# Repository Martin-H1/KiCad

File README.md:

# KiCad

I will post my open source PCB designs here.

Overview
======
The purpose of this repository is to serve as a backup of my projects, as well as a way to

Prerequisites
======
* KiCad 7.0
* Git to fetch these files.

Directories
======
* Mench Reloaded - w65c265 SBC specs similar to the Mench computer from WDC.
* README.md - this file.

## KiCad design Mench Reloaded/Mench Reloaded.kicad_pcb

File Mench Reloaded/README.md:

# Mench Reloaded

A single board computer with specs similar or better than the Mench computer from WDC.

Features Include
======
* W65C265 Microcontroller featuring the W65C816 core microprocessor
* 1 W65C22 Versatile Interface Adapters
* 128KB or 256KB SRAM
* 32K EEPROM
* Expansion headers that match the W65C265SXB.
* 65c22 GPIO headers that match the SBC-2 by Daryl Rictor.
* FTDI for serial interface and optional power.
* Optional battery power.

Prerequisites
======
* KiCad 9.0
* Git to fetch these files.

Notes
======
* Documentation for the w65c265 and Mench computer are available on the WDC website:
* https://www.westerndesigncenter.com/wdc/documentation/w65c265s.pdf
* https://www.westerndesigncenter.com/wdc/Schematics/W65C265SXB.pdf
* https://www.westerndesigncenter.com/wdc/Mensch_Computer.php

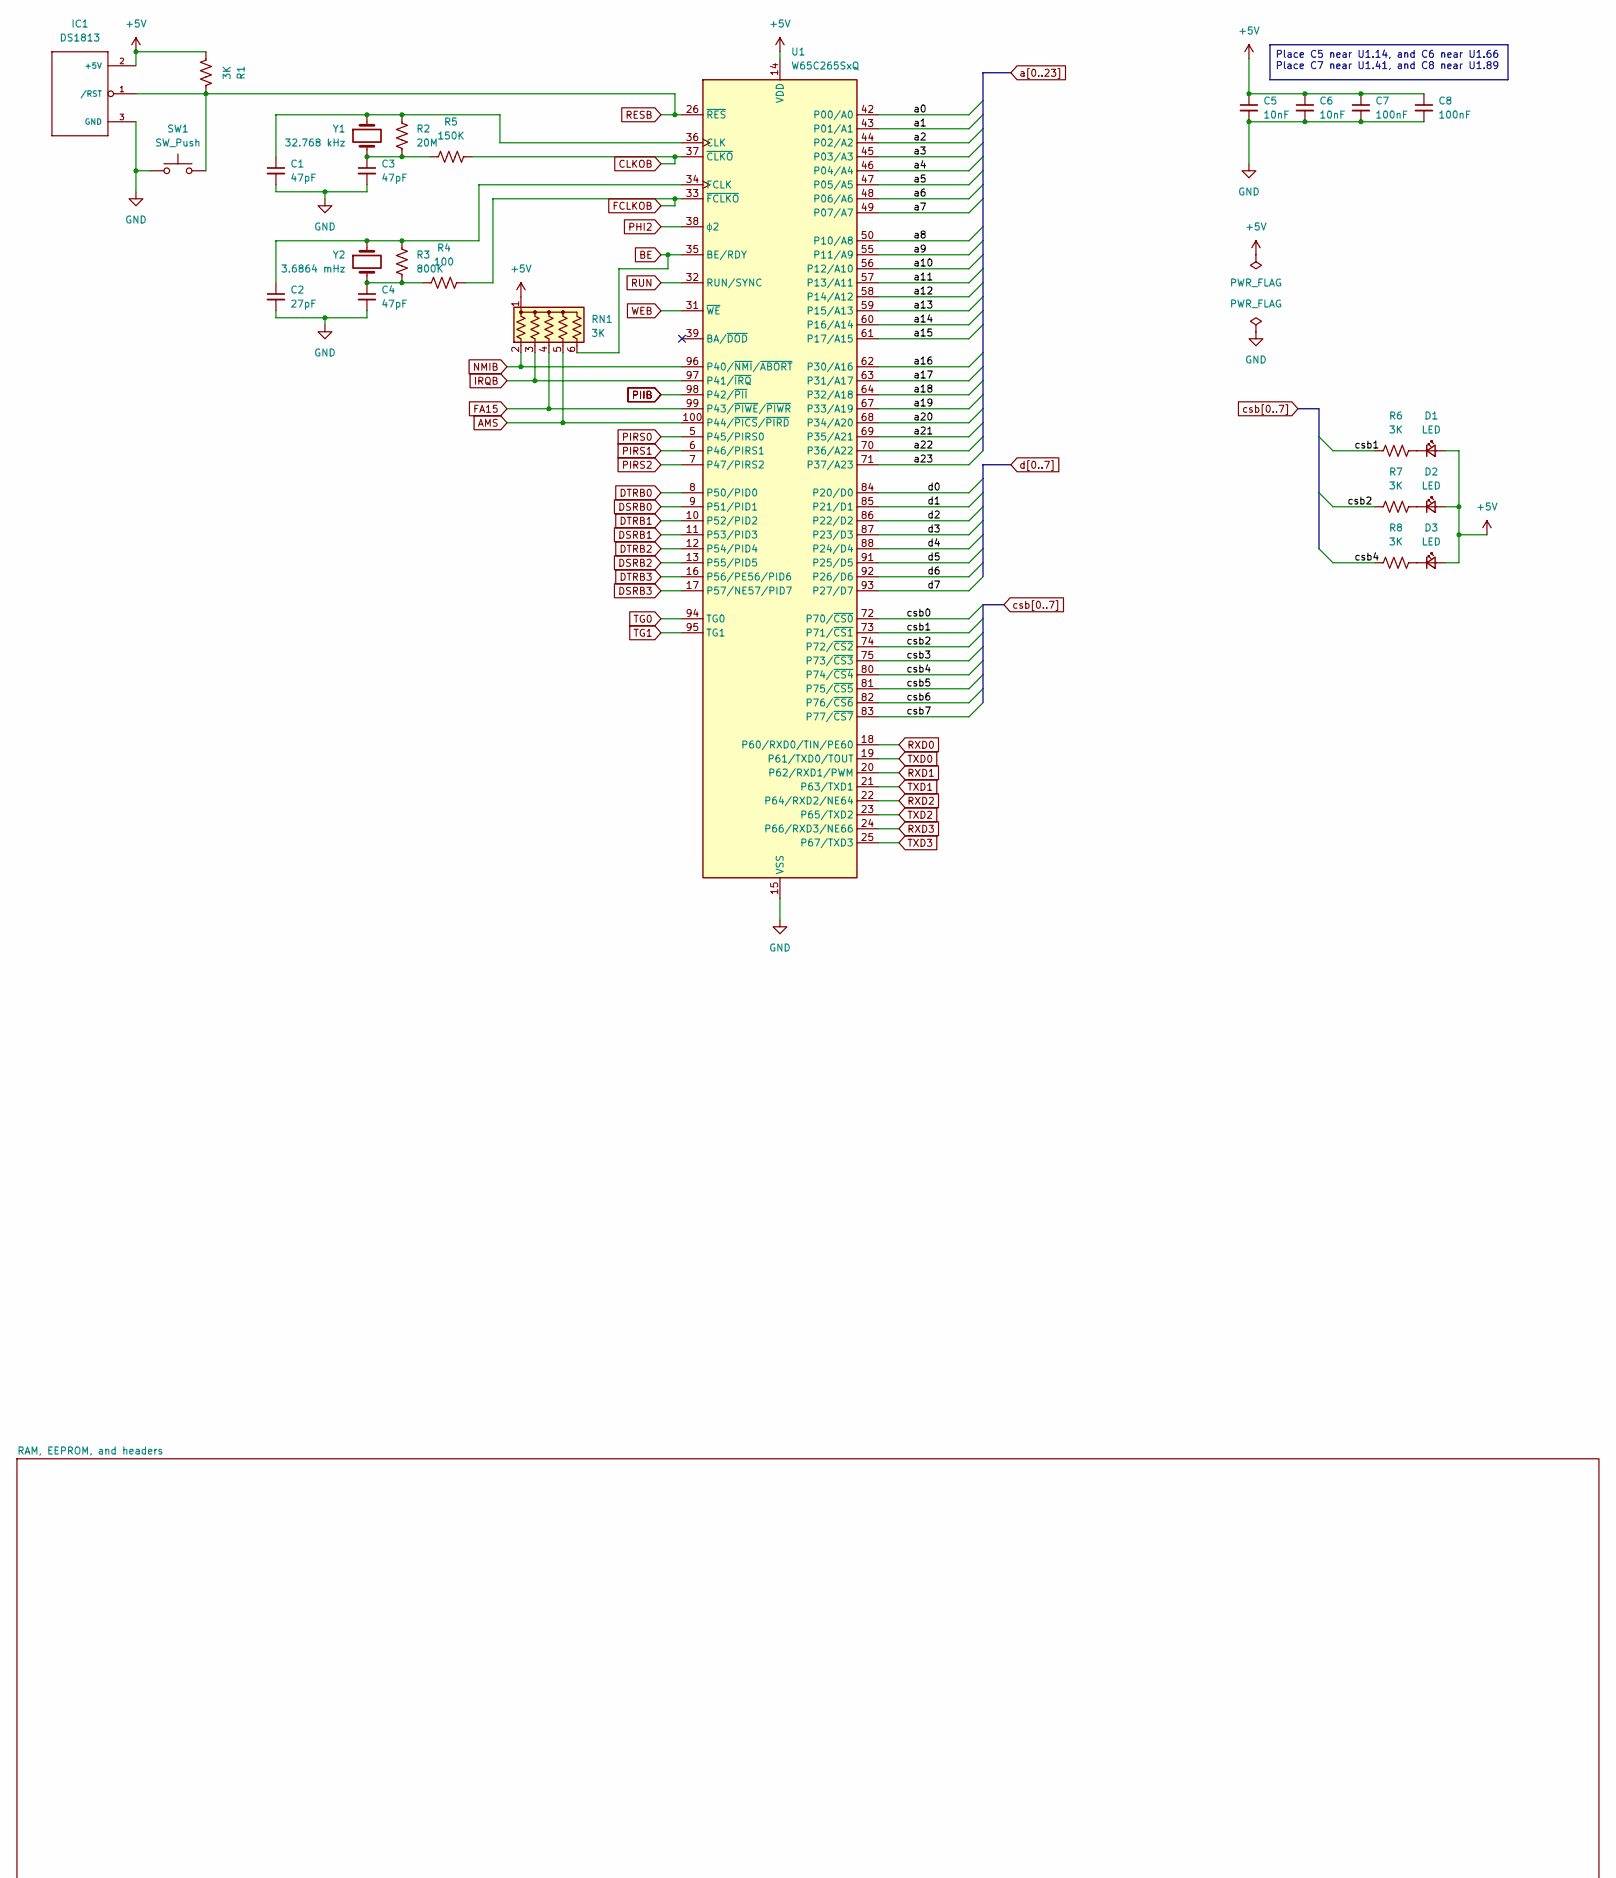
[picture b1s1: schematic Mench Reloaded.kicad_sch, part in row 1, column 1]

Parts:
C1, C3, C4: 47pF; C_0805_2012Metric_Pad1.18x1.45mm_HandSolder
C2: 27pF; C_0805_2012Metric_Pad1.18x1.45mm_HandSolder
C5, C6: 10nF; C_0805_2012Metric_Pad1.18x1.45mm_HandSolder
C7, C8: 100nF; C_0805_2012Metric_Pad1.18x1.45mm_HandSolder
D1, D2, D3: LED; LED_0805_2012Metric_Pad1.15x1.40mm_HandSolder
IC1: DS1813; ds1813_revised-TO-92
R1, R6, R7, R8: 3K; R_0805_2012Metric_Pad1.20x1.40mm_HandSolder
R2: 20M; R_0805_2012Metric_Pad1.20x1.40mm_HandSolder
R3: 800K; R_0805_2012Metric_Pad1.20x1.40mm_HandSolder
R4: 100; R_0805_2012Metric_Pad1.20x1.40mm_HandSolder
R5: 150K; R_0805_2012Metric_Pad1.20x1.40mm_HandSolder
RN1: 3K; R_Array_SIP6
SW1: SW_Push; SW_PUSH_6mm_H5mm
U1: W65C265SxQ; PQFP-100_14x20mm_P0.65mm_HandSolder
Y1: 32.768 kHz; Crystal_C26-LF_D2.1mm_L6.5mm_Horizontal
Y2: 3.6864 mHz; Crystal_HC49-U_Vertical

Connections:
+5V: C5.1, C6.1, C7.1, C8.1, D1.2 (A), D2.2 (A), D3.2 (A), IC1.2 (+5V), R1.2, RN1.1 (common), U1.14 (VDD), U1.41 (VDD), U1.66 (VDD), U1.89 (VDD); also elsewhere on the board
AMS: RN1.5 (R4), U1.100 (P44/~PICS/~PIRD); also elsewhere on the board
BE: RN1.6 (R5), U1.35 (BE/RDY); also elsewhere on the board
CLKOB: R5.2, U1.37 (~CLKO); also elsewhere on the board
DSRB0: U1.9 (P51/PID1); also elsewhere on the board
DSRB1: U1.11 (P53/PID3); also elsewhere on the board
DSRB2: U1.13 (P55/PID5); also elsewhere on the board
DSRB3: U1.17 (P57/NE57/PID7); also elsewhere on the board
DTRB0: U1.8 (P50/PID0); also elsewhere on the board
DTRB1: U1.10 (P52/PID2); also elsewhere on the board
DTRB2: U1.12 (P54/PID4); also elsewhere on the board
DTRB3: U1.16 (P56/PE56/PID6); also elsewhere on the board
FA15: RN1.4 (R3), U1.99 (P43/~PIWE/~PIWR); also elsewhere on the board
FCLKOB: R4.2, U1.33 (~FCLKO); also elsewhere on the board
GND: C1.2, C2.2, C3.2, C4.2, C5.2, C6.2, C7.2, C8.2, IC1.3 (GND), SW1.1, U1.15 (VSS), U1.40 (VSS), U1.65 (VSS), U1.90 (VSS); also elsewhere on the board
IRQB: RN1.3 (R2), U1.97 (P41/~IRQ); also elsewhere on the board
NMIB: RN1.2 (R1), U1.96 (P40/~NMI/~ABORT); also elsewhere on the board
unnamed: C3.1, R2.1, R5.1, Y1.2
unnamed: C4.1, R3.1, R4.1, Y2.2
unnamed: D1.1 (K), R6.2
unnamed: D2.1 (K), R7.2
unnamed: D3.1 (K), R8.2
unnamed: C1.1, R2.2, U1.36 (CLK), Y1.1
unnamed: C2.1, R3.2, U1.34 (FCLK), Y2.1
PHI2: U1.38 (ϕ2); also elsewhere on the board
PIIB: U1.98 (P42/~PII); also elsewhere on the board
PIRS0: U1.5 (P45/PIRS0); also elsewhere on the board
PIRS1: U1.6 (P46/PIRS1); also elsewhere on the board
PIRS2: U1.7 (P47/PIRS2); also elsewhere on the board
RESB: IC1.1 (/RST), R1.1, SW1.2, U1.26 (~RES); also elsewhere on the board
RUN: U1.32 (RUN/SYNC); also elsewhere on the board
RXD0: U1.18 (P60/RXD0/TIN/PE60); also elsewhere on the board
RXD1: U1.20 (P62/RXD1/PWM); also elsewhere on the board
RXD2: U1.22 (P64/RXD2/NE64); also elsewhere on the board
RXD3: U1.24 (P66/RXD3/NE66); also elsewhere on the board
TG0: U1.94 (TG0); also elsewhere on the board
TG1: U1.95 (TG1); also elsewhere on the board
TXD0: U1.19 (P61/TXD0/TOUT); also elsewhere on the board
TXD1: U1.21 (P63/TXD1); also elsewhere on the board
TXD2: U1.23 (P65/TXD2); also elsewhere on the board
TXD3: U1.25 (P67/TXD3); also elsewhere on the board
WEB: U1.31 (~WE); also elsewhere on the board
a0: U1.42 (P00/A0); also elsewhere on the board
a1: U1.43 (P01/A1); also elsewhere on the board
a2: U1.44 (P02/A2); also elsewhere on the board
a3: U1.45 (P03/A3); also elsewhere on the board
a4: U1.46 (P04/A4); also elsewhere on the board
a5: U1.47 (P05/A5); also elsewhere on the board
a6: U1.48 (P06/A6); also elsewhere on the board
a7: U1.49 (P07/A7); also elsewhere on the board
a8: U1.50 (P10/A8); also elsewhere on the board
a9: U1.55 (P11/A9); also elsewhere on the board
a10: U1.56 (P12/A10); also elsewhere on the board
a11: U1.57 (P13/A11); also elsewhere on the board
a12: U1.58 (P14/A12); also elsewhere on the board
a13: U1.59 (P15/A13); also elsewhere on the board
a14: U1.60 (P16/A14); also elsewhere on the board
a15: U1.61 (P17/A15); also elsewhere on the board
a16: U1.62 (P30/A16); also elsewhere on the board
a17: U1.63 (P31/A17); also elsewhere on the board
a18: U1.64 (P32/A18); also elsewhere on the board
a19: U1.67 (P33/A19); also elsewhere on the board
a20: U1.68 (P34/A20); also elsewhere on the board
a21: U1.69 (P35/A21); also elsewhere on the board
a22: U1.70 (P36/A22); also elsewhere on the board
a23: U1.71 (P37/A23); also elsewhere on the board
csb0: U1.72 (P70/~CS0); also elsewhere on the board
csb1: R6.1, U1.73 (P71/~CS1); also elsewhere on the board
csb2: R7.1, U1.74 (P72/~CS2)
csb3: U1.75 (P73/~CS3); also elsewhere on the board
csb4: R8.1, U1.80 (P74/~CS4); also elsewhere on the board
csb5: U1.81 (P75/~CS5); also elsewhere on the board
csb6: U1.82 (P76/~CS6); also elsewhere on the board
csb7: U1.83 (P77/~CS7); also elsewhere on the board
d0: U1.84 (P20/D0); also elsewhere on the board
d1: U1.85 (P21/D1); also elsewhere on the board
d2: U1.86 (P22/D2); also elsewhere on the board
d3: U1.87 (P23/D3); also elsewhere on the board
d4: U1.88 (P24/D4); also elsewhere on the board
d5: U1.91 (P25/D5); also elsewhere on the board
d6: U1.92 (P26/D6); also elsewhere on the board
d7: U1.93 (P27/D7); also elsewhere on the board

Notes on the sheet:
Place C5 near U1.14, and C6 near U1.66 Place C7 near U1.41, and C8 near U1.89

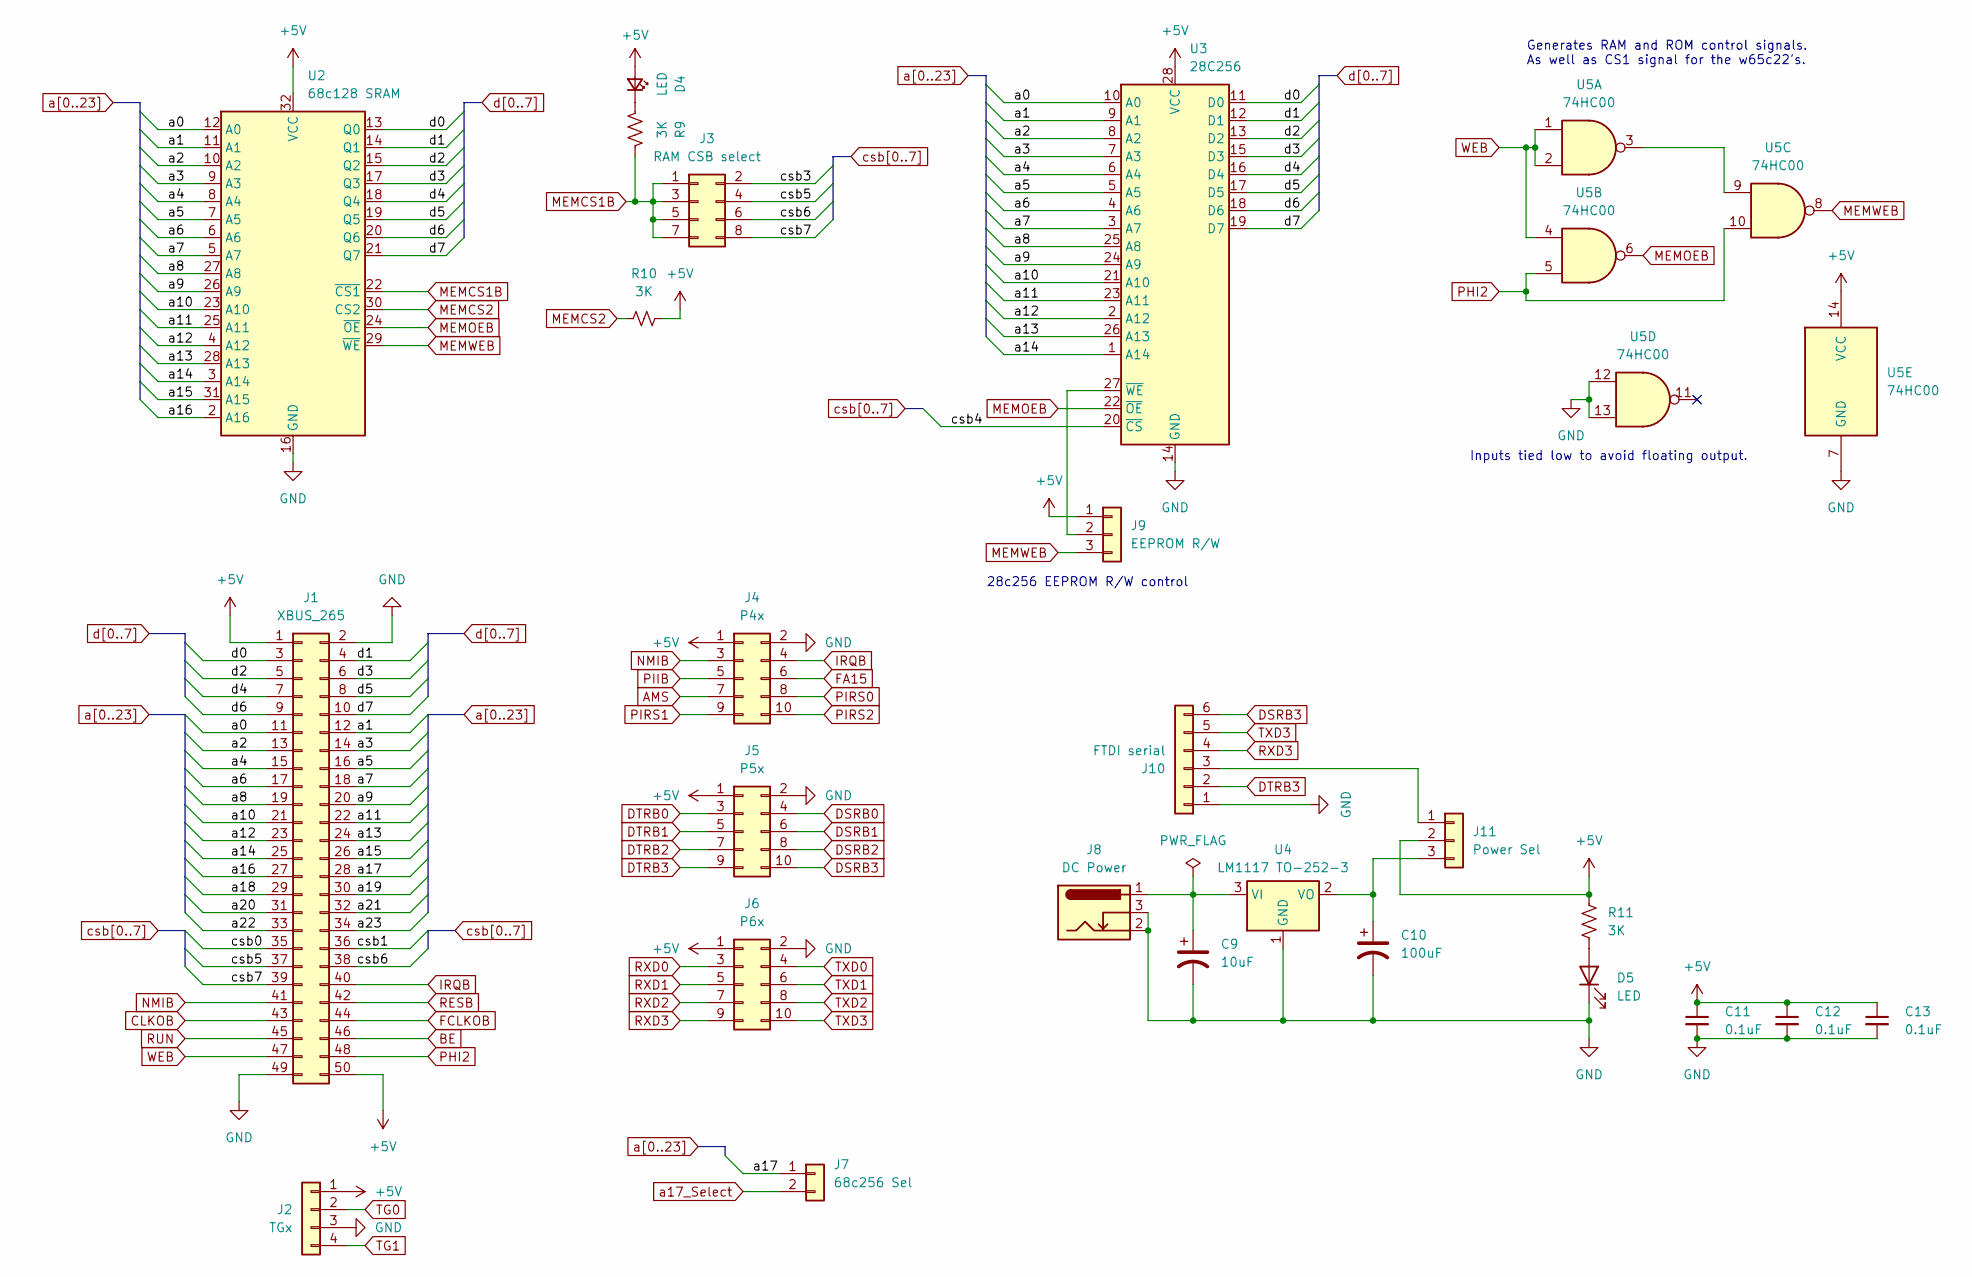
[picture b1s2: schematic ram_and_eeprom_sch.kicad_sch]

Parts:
C9: 10uF; CP_Radial_D5.0mm_P2.50mm
C10: 100uF; CP_Radial_D5.0mm_P2.50mm
C11, C12, C13: 0.1uF; C_0805_2012Metric_Pad1.18x1.45mm_HandSolder
D4, D5: LED; LED_0805_2012Metric_Pad1.15x1.40mm_HandSolder
J1: XBUS_265; PinHeader_2x25_P2.54mm_Vertical
J2: TGx; PinHeader_1x04_P2.54mm_Vertical
J3: RAM CSB select; PinHeader_2x04_P2.54mm_Vertical
J4: P4x; PinHeader_2x05_P2.54mm_Vertical
J5: P5x; PinHeader_2x05_P2.54mm_Vertical
J6: P6x; PinHeader_2x05_P2.54mm_Vertical
J7: 68c256 Sel; PinHeader_1x02_P2.54mm_Vertical
J8: DC Power; BarrelJack_Horizontal
J9: EEPROM R/W; PinHeader_1x03_P2.54mm_Vertical
J10: FTDI serial; PinHeader_1x06_P2.54mm_Horizontal
J11: Power Sel; PinHeader_1x03_P2.54mm_Vertical
R9, R10, R11: 3K; R_0805_2012Metric_Pad1.20x1.40mm_HandSolder
U2: 68c128 SRAM; DIP-32_W15.24mm_Socket
U3: 28C256; DIP-28_W15.24mm_LowProfileZifSocket
U4: LM1117 TO-252-3; TO-252-3_TabPin2
U5: 74HC00; SOIC-14_3.9x8.7mm_P1.27mm

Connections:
+5V: C11.1, C12.1, C13.1, D4.2 (A), J1.1, J1.50, J2.1, J4.1, J5.1, J6.1, J9.1, J11.2, R10.1, R11.1, U2.32 (VCC), U3.28 (VCC), U5.14 (VCC); also elsewhere on the board
AMS: J4.7; also elsewhere on the board
BE: J1.46; also elsewhere on the board
CLKOB: J1.43; also elsewhere on the board
DSRB0: J5.4; also elsewhere on the board
DSRB1: J5.6; also elsewhere on the board
DSRB2: J5.8; also elsewhere on the board
DSRB3: J5.10, J10.6; also elsewhere on the board
DTRB0: J5.3; also elsewhere on the board
DTRB1: J5.5; also elsewhere on the board
DTRB2: J5.7; also elsewhere on the board
DTRB3: J5.9, J10.2; also elsewhere on the board
FA15: J4.6; also elsewhere on the board
FCLKOB: J1.44; also elsewhere on the board
GND: C9.2, C10.2, C11.2, C12.2, C13.2, D5.1 (K), J1.2, J1.49, J2.3, J4.2, J5.2, J6.2, J8.2, J8.3, J10.1, U2.16 (GND), U3.14 (GND), U4.1 (GND), U5.7 (GND), U5.12, U5.13; also elsewhere on the board
IRQB: J1.40, J4.4; also elsewhere on the board
MEMCS1B: J3.1, J3.3, J3.5, J3.7, R9.1, U2.22 (~CS1)
MEMCS2: R10.2, U2.30 (CS2)
MEMOEB: U2.24 (~OE), U3.22 (~OE), U5.6
MEMWEB: J9.3, U2.29 (~WE), U5.8
NMIB: J1.41, J4.3; also elsewhere on the board
unnamed: D4.1 (K), R9.2
unnamed: D5.2 (A), R11.2
unnamed: J9.2, U3.27 (~WE)
unnamed: J10.3, J11.1
unnamed: C10.1, J11.3, U4.2 (VO)
unnamed: C9.1, J8.1, U4.3 (VI)
unnamed: U5.3, U5.9
PHI2: J1.48, U5.5, U5.10; also elsewhere on the board
PIIB: J4.5; also elsewhere on the board
PIRS0: J4.8; also elsewhere on the board
PIRS1: J4.9; also elsewhere on the board
PIRS2: J4.10; also elsewhere on the board
RESB: J1.42; also elsewhere on the board
RUN: J1.45; also elsewhere on the board
RXD0: J6.3; also elsewhere on the board
RXD1: J6.5; also elsewhere on the board
RXD2: J6.7; also elsewhere on the board
RXD3: J6.9, J10.4; also elsewhere on the board
TG0: J2.2; also elsewhere on the board
TG1: J2.4; also elsewhere on the board
TXD0: J6.4; also elsewhere on the board
TXD1: J6.6; also elsewhere on the board
TXD2: J6.8; also elsewhere on the board
TXD3: J6.10, J10.5; also elsewhere on the board
WEB: J1.47, U5.1, U5.2, U5.4; also elsewhere on the board
a0: J1.11, U2.12 (A0), U3.10 (A0); also elsewhere on the board
a1: J1.12, U2.11 (A1), U3.9 (A1); also elsewhere on the board
a2: J1.13, U2.10 (A2), U3.8 (A2); also elsewhere on the board
a3: J1.14, U2.9 (A3), U3.7 (A3); also elsewhere on the board
a4: J1.15, U2.8 (A4), U3.6 (A4); also elsewhere on the board
a5: J1.16, U2.7 (A5), U3.5 (A5); also elsewhere on the board
a6: J1.17, U2.6 (A6), U3.4 (A6); also elsewhere on the board
a7: J1.18, U2.5 (A7), U3.3 (A7); also elsewhere on the board
a8: J1.19, U2.27 (A8), U3.25 (A8); also elsewhere on the board
a9: J1.20, U2.26 (A9), U3.24 (A9); also elsewhere on the board
a10: J1.21, U2.23 (A10), U3.21 (A10); also elsewhere on the board
a11: J1.22, U2.25 (A11), U3.23 (A11); also elsewhere on the board
a12: J1.23, U2.4 (A12), U3.2 (A12); also elsewhere on the board
a13: J1.24, U2.28 (A13), U3.26 (A13); also elsewhere on the board
a14: J1.25, U2.3 (A14), U3.1 (A14); also elsewhere on the board
a15: J1.26, U2.31 (A15); also elsewhere on the board
a16: J1.27, U2.2 (A16); also elsewhere on the board
a17: J1.28, J7.1; also elsewhere on the board
a17_Select: J7.2, U2.1 (NC)
a18: J1.29; also elsewhere on the board
a19: J1.30; also elsewhere on the board
a20: J1.31; also elsewhere on the board
a21: J1.32; also elsewhere on the board
a22: J1.33; also elsewhere on the board
a23: J1.34; also elsewhere on the board
csb0: J1.35; also elsewhere on the board
csb1: J1.36; also elsewhere on the board
csb3: J3.2; also elsewhere on the board
csb4: U3.20 (~CS); also elsewhere on the board
csb5: J1.37, J3.4; also elsewhere on the board
csb6: J1.38, J3.6; also elsewhere on the board
csb7: J1.39, J3.8; also elsewhere on the board
d0: J1.3, U2.13 (Q0), U3.11 (D0); also elsewhere on the board
d1: J1.4, U2.14 (Q1), U3.12 (D1); also elsewhere on the board
d2: J1.5, U2.15 (Q2), U3.13 (D2); also elsewhere on the board
d3: J1.6, U2.17 (Q3), U3.15 (D3); also elsewhere on the board
d4: J1.7, U2.18 (Q4), U3.16 (D4); also elsewhere on the board
d5: J1.8, U2.19 (Q5), U3.17 (D5); also elsewhere on the board
d6: J1.9, U2.20 (Q6), U3.18 (D6); also elsewhere on the board
d7: J1.10, U2.21 (Q7), U3.19 (D7); also elsewhere on the board

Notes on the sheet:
28c256 EEPROM R/W control
Inputs tied low to avoid floating output.
Generates RAM and ROM control signals. As well as CS1 signal for the w65c22's.

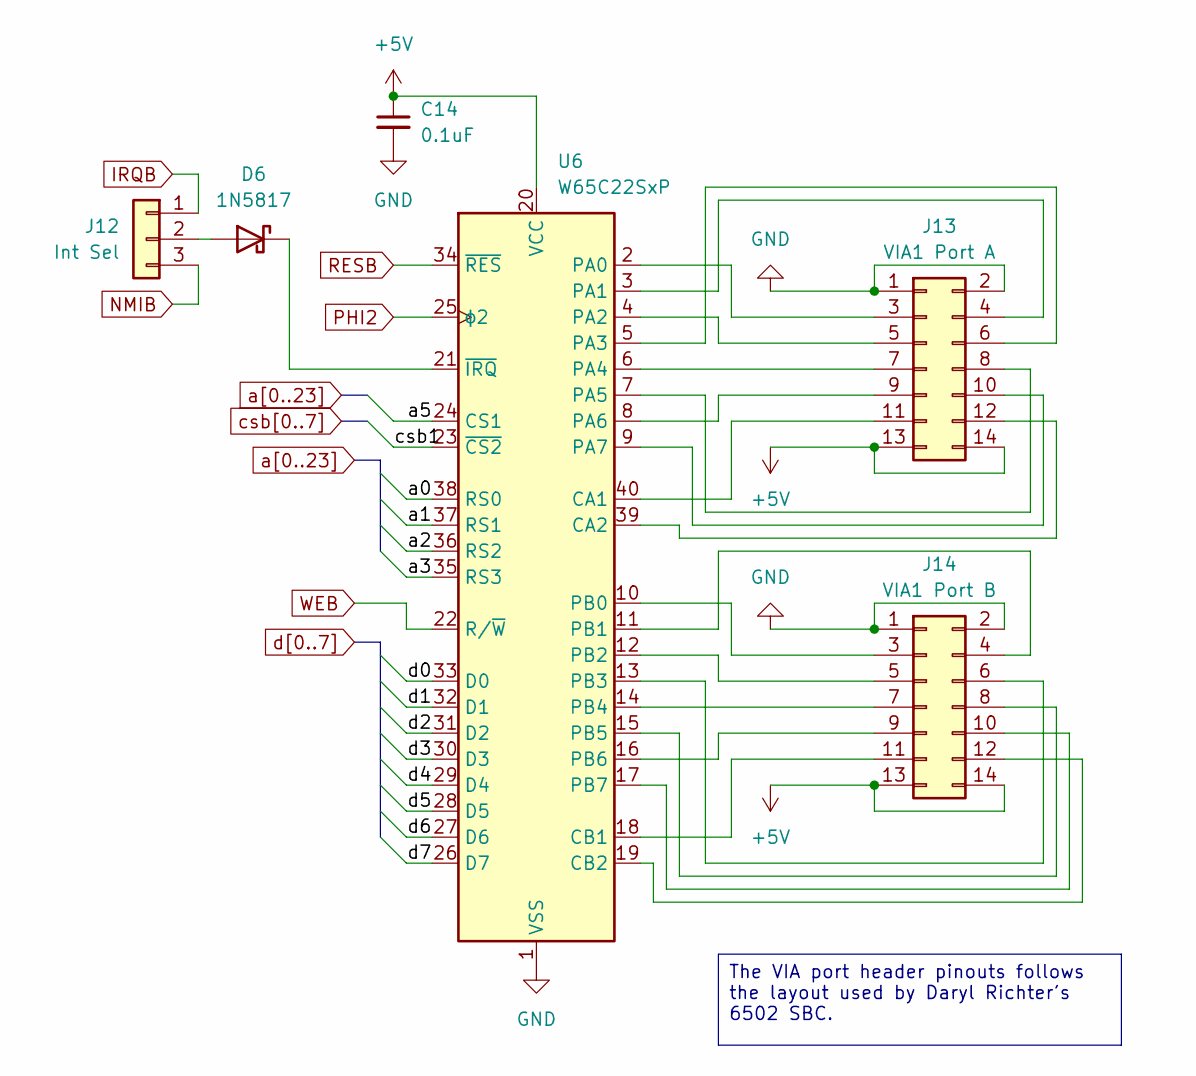
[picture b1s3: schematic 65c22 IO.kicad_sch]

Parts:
C14: 0.1uF; C_0805_2012Metric_Pad1.18x1.45mm_HandSolder
D6: 1N5817; D_DO-41_SOD81_P10.16mm_Horizontal
J12: Int Sel; PinHeader_1x03_P2.54mm_Vertical
J13: VIA1 Port A; PinHeader_2x07_P2.54mm_Vertical
J14: VIA1 Port B; PinHeader_2x07_P2.54mm_Vertical
U6: W65C22SxP; DIP-40_W15.24mm

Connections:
+5V: C14.1, J13.13, J13.14, J14.13, J14.14, U6.20 (VCC); also elsewhere on the board
GND: C14.2, J13.1, J13.2, J14.1, J14.2, U6.1 (VSS); also elsewhere on the board
IRQB: J12.1; also elsewhere on the board
NMIB: J12.3; also elsewhere on the board
unnamed: D6.2 (A), J12.2
unnamed: D6.1 (K), U6.21 (~IRQ)
unnamed: J13.3, U6.2 (PA0)
unnamed: J13.4, U6.3 (PA1)
unnamed: J13.5, U6.4 (PA2)
unnamed: J13.6, U6.5 (PA3)
unnamed: J13.7, U6.6 (PA4)
unnamed: J13.8, U6.7 (PA5)
unnamed: J13.9, U6.8 (PA6)
unnamed: J13.10, U6.9 (PA7)
unnamed: J13.11, U6.40 (CA1)
unnamed: J13.12, U6.39 (CA2)
unnamed: J14.3, U6.10 (PB0)
unnamed: J14.4, U6.11 (PB1)
unnamed: J14.5, U6.12 (PB2)
unnamed: J14.6, U6.13 (PB3)
unnamed: J14.7, U6.14 (PB4)
unnamed: J14.8, U6.15 (PB5)
unnamed: J14.9, U6.16 (PB6)
unnamed: J14.10, U6.17 (PB7)
unnamed: J14.11, U6.18 (CB1)
unnamed: J14.12, U6.19 (CB2)
PHI2: U6.25 (ϕ2); also elsewhere on the board
RESB: U6.34 (~RES); also elsewhere on the board
WEB: U6.22 (R/~W); also elsewhere on the board
a0: U6.38 (RS0); also elsewhere on the board
a1: U6.37 (RS1); also elsewhere on the board
a2: U6.36 (RS2); also elsewhere on the board
a3: U6.35 (RS3); also elsewhere on the board
a5: U6.24 (CS1); also elsewhere on the board
csb1: U6.23 (~CS2); also elsewhere on the board
d0: U6.33 (D0); also elsewhere on the board
d1: U6.32 (D1); also elsewhere on the board
d2: U6.31 (D2); also elsewhere on the board
d3: U6.30 (D3); also elsewhere on the board
d4: U6.29 (D4); also elsewhere on the board
d5: U6.28 (D5); also elsewhere on the board
d6: U6.27 (D6); also elsewhere on the board
d7: U6.26 (D7); also elsewhere on the board

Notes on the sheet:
The VIA port header pinouts follows the layout used by Daryl Richter's 6502 SBC.

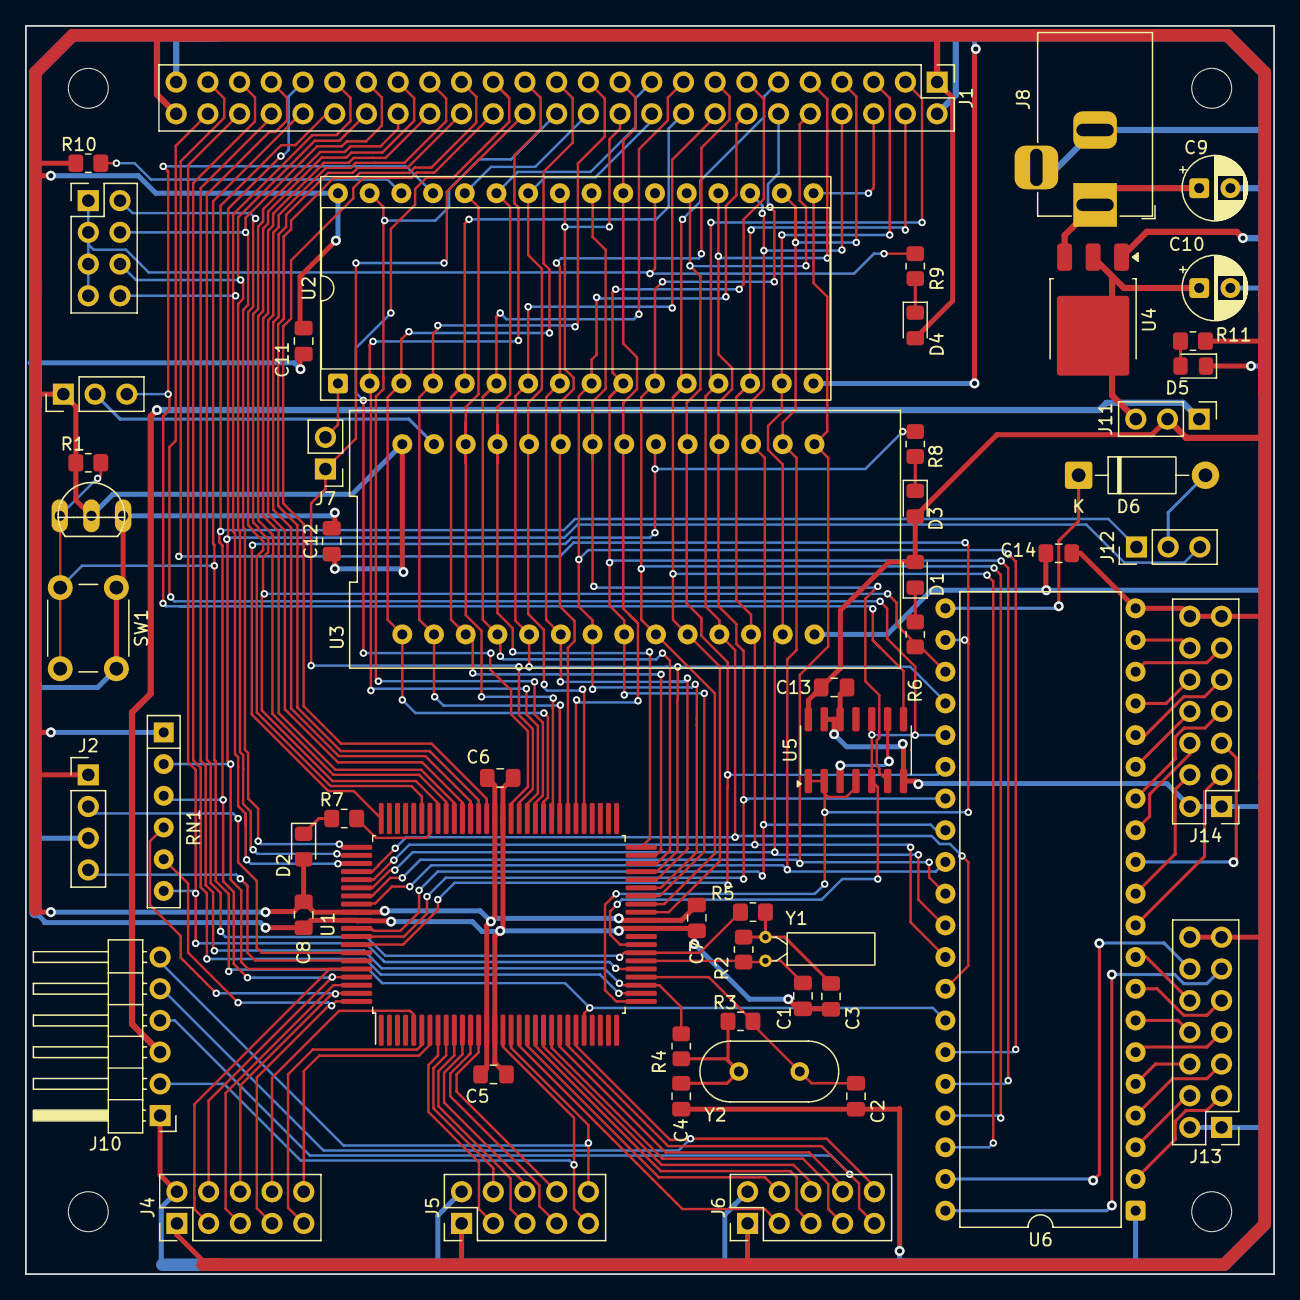
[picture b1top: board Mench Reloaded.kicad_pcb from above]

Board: 2 copper layers, 100.0 x 100.0 mm, 60 parts (0 on the bottom side), 116 nets.

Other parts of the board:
MH1, MH2, MH3, MH4: MountingHole_3.2mm_M3_DIN965

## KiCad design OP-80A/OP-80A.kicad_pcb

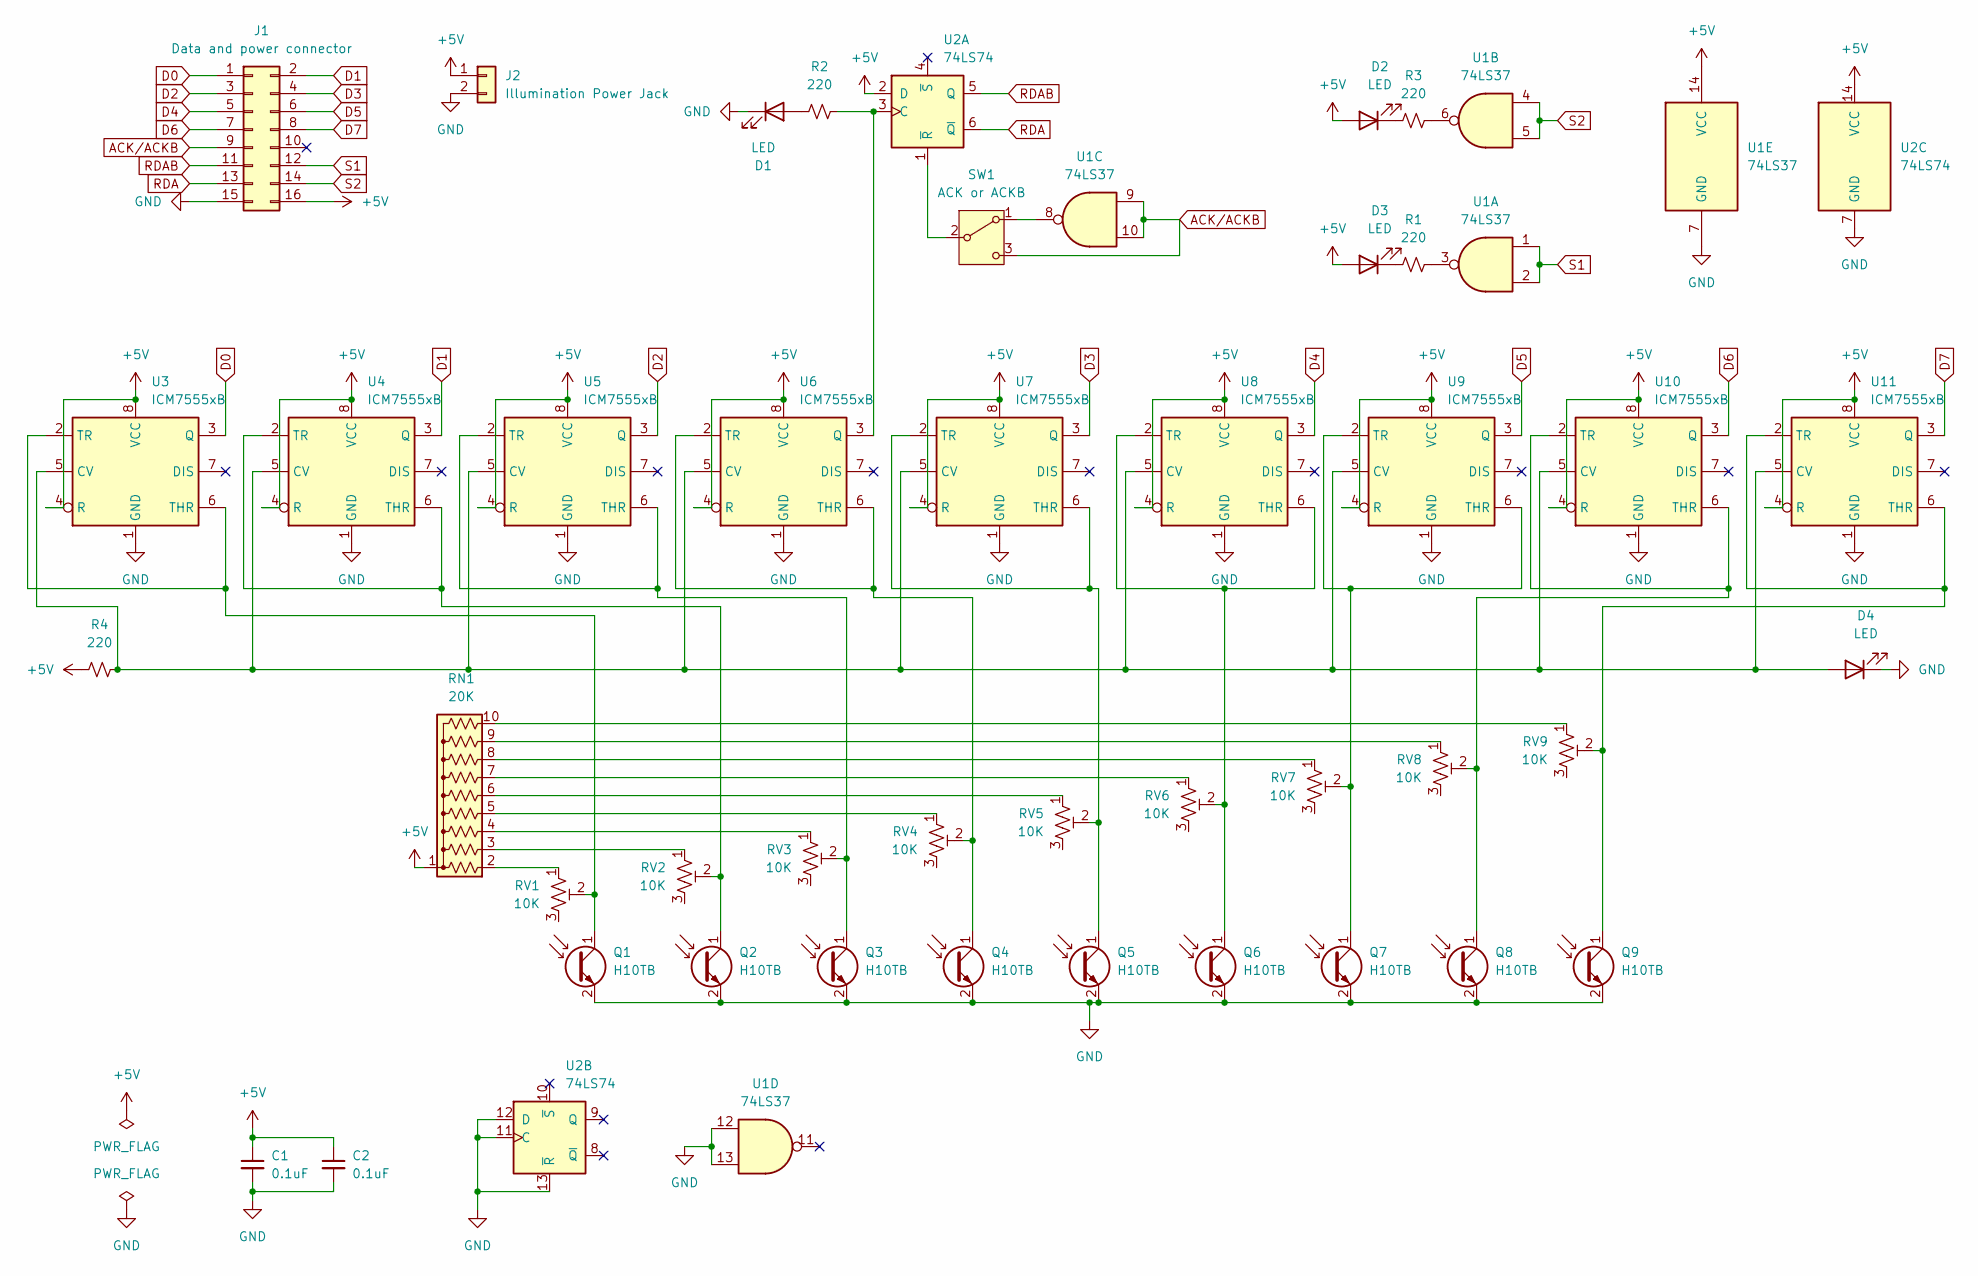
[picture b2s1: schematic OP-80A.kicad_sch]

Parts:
C1, C2: 0.1uF; C_Disc_D3.0mm_W1.6mm_P2.50mm
D1, D2, D3, D4: LED; LED_D5.0mm
J1: Data and power connector; PinSocket_2x08_P2.54mm_Vertical
J2: Illumination Power Jack; TerminalBlock_4Ucon_1x02_P3.50mm_Horizontal
Q1, Q2, Q3, Q4, Q5, Q6, Q7, Q8, Q9: H10TB; LED_0805_2012Metric_Pad1.15x1.40mm_HandSolder
R1, R2, R3, R4: 220; R_Axial_DIN0204_L3.6mm_D1.6mm_P7.62mm_Horizontal
RN1: 20K; R_Array_SIP10
RV1, RV2, RV3, RV4, RV5, RV6, RV7, RV8, RV9: 10K; Potentiometer_Runtron_RM-065_Vertical
SW1: ACK or ACKB; SW_Slide-03_Wuerth-WS-SLTV_10x2.5x6.4_P2.54mm
U1: 74LS37; SO-14_5.3x10.2mm_P1.27mm
U2: 74LS74; SO-14_5.3x10.2mm_P1.27mm
U3, U4, U5, U6, U7, U8, U9, U10, U11: ICM7555xB; SOIC-8_3.9x4.9mm_P1.27mm

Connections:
+5V: C1.1, C2.1, D2.2 (A), D3.2 (A), J1.16, J2.1, R4.1, RN1.1 (common), U1.14 (VCC), U2.2 (D), U2.14 (VCC), U3.4 (R), U3.8 (VCC), U4.4 (R), U4.8 (VCC), U5.4 (R), U5.8 (VCC), U6.4 (R), U6.8 (VCC), U7.4 (R), U7.8 (VCC), U8.4 (R), U8.8 (VCC), U9.4 (R), U9.8 (VCC), U10.4 (R), U10.8 (VCC), U11.4 (R), U11.8 (VCC)
ACK/ACKB: J1.9, SW1.3 (C), U1.9, U1.10
D0: J1.1, U3.3 (Q)
D1: J1.2, U4.3 (Q)
D2: J1.3, U5.3 (Q)
D3: J1.4, U7.3 (Q)
D4: J1.5, U8.3 (Q)
D5: J1.6, U9.3 (Q)
D6: J1.7, U10.3 (Q)
D7: J1.8, U11.3 (Q)
GND: C1.2, C2.2, D1.1 (K), D4.1 (K), J1.15, J2.2, Q1.2 (E), Q2.2 (E), Q3.2 (E), Q4.2 (E), Q5.2 (E), Q6.2 (E), Q7.2 (E), Q8.2 (E), Q9.2 (E), U1.7 (GND), U1.12, U1.13, U2.7 (GND), U2.11 (C), U2.12 (D), U2.13 (~R), U3.1 (GND), U4.1 (GND), U5.1 (GND), U6.1 (GND), U7.1 (GND), U8.1 (GND), U9.1 (GND), U10.1 (GND), U11.1 (GND)
unnamed: D1.2 (A), R2.1
unnamed: D2.1 (K), R3.1
unnamed: D3.1 (K), R1.1
unnamed: D4.2 (A), R4.2, U3.5 (CV), U4.5 (CV), U5.5 (CV), U6.5 (CV), U7.5 (CV), U8.5 (CV), U9.5 (CV), U10.5 (CV), U11.5 (CV)
unnamed: Q1.1 (C), RV1.2, U3.2 (TR), U3.6 (THR)
unnamed: Q2.1 (C), RV2.2, U4.2 (TR), U4.6 (THR)
unnamed: Q3.1 (C), RV3.2, U5.2 (TR), U5.6 (THR)
unnamed: Q4.1 (C), RV4.2, U6.2 (TR), U6.6 (THR)
unnamed: Q5.1 (C), RV5.2, U7.2 (TR), U7.6 (THR)
unnamed: Q6.1 (C), RV6.2, U8.2 (TR), U8.6 (THR)
unnamed: Q7.1 (C), RV7.2, U9.2 (TR), U9.6 (THR)
unnamed: Q8.1 (C), RV8.2, U10.2 (TR), U10.6 (THR)
unnamed: Q9.1 (C), RV9.2, U11.2 (TR), U11.6 (THR)
unnamed: R1.2, U1.3
unnamed: R3.2, U1.6
unnamed: RN1.2 (R1), RV1.1
unnamed: RN1.3 (R2), RV2.1
unnamed: RN1.4 (R3), RV3.1
unnamed: RN1.5 (R4), RV4.1
unnamed: RN1.6 (R5), RV5.1
unnamed: RN1.7 (R6), RV6.1
unnamed: RN1.8 (R7), RV7.1
unnamed: RN1.9 (R8), RV8.1
unnamed: RN1.10 (R9), RV9.1
unnamed: SW1.1 (A), U1.8
unnamed: SW1.2 (B), U2.1 (~R)
unnamed: R2.2, U2.3 (C), U6.3 (Q)
RDA: J1.13, U2.6 (~Q)
RDAB: J1.11, U2.5 (Q)
S1: J1.12, U1.1, U1.2
S2: J1.14, U1.4, U1.5

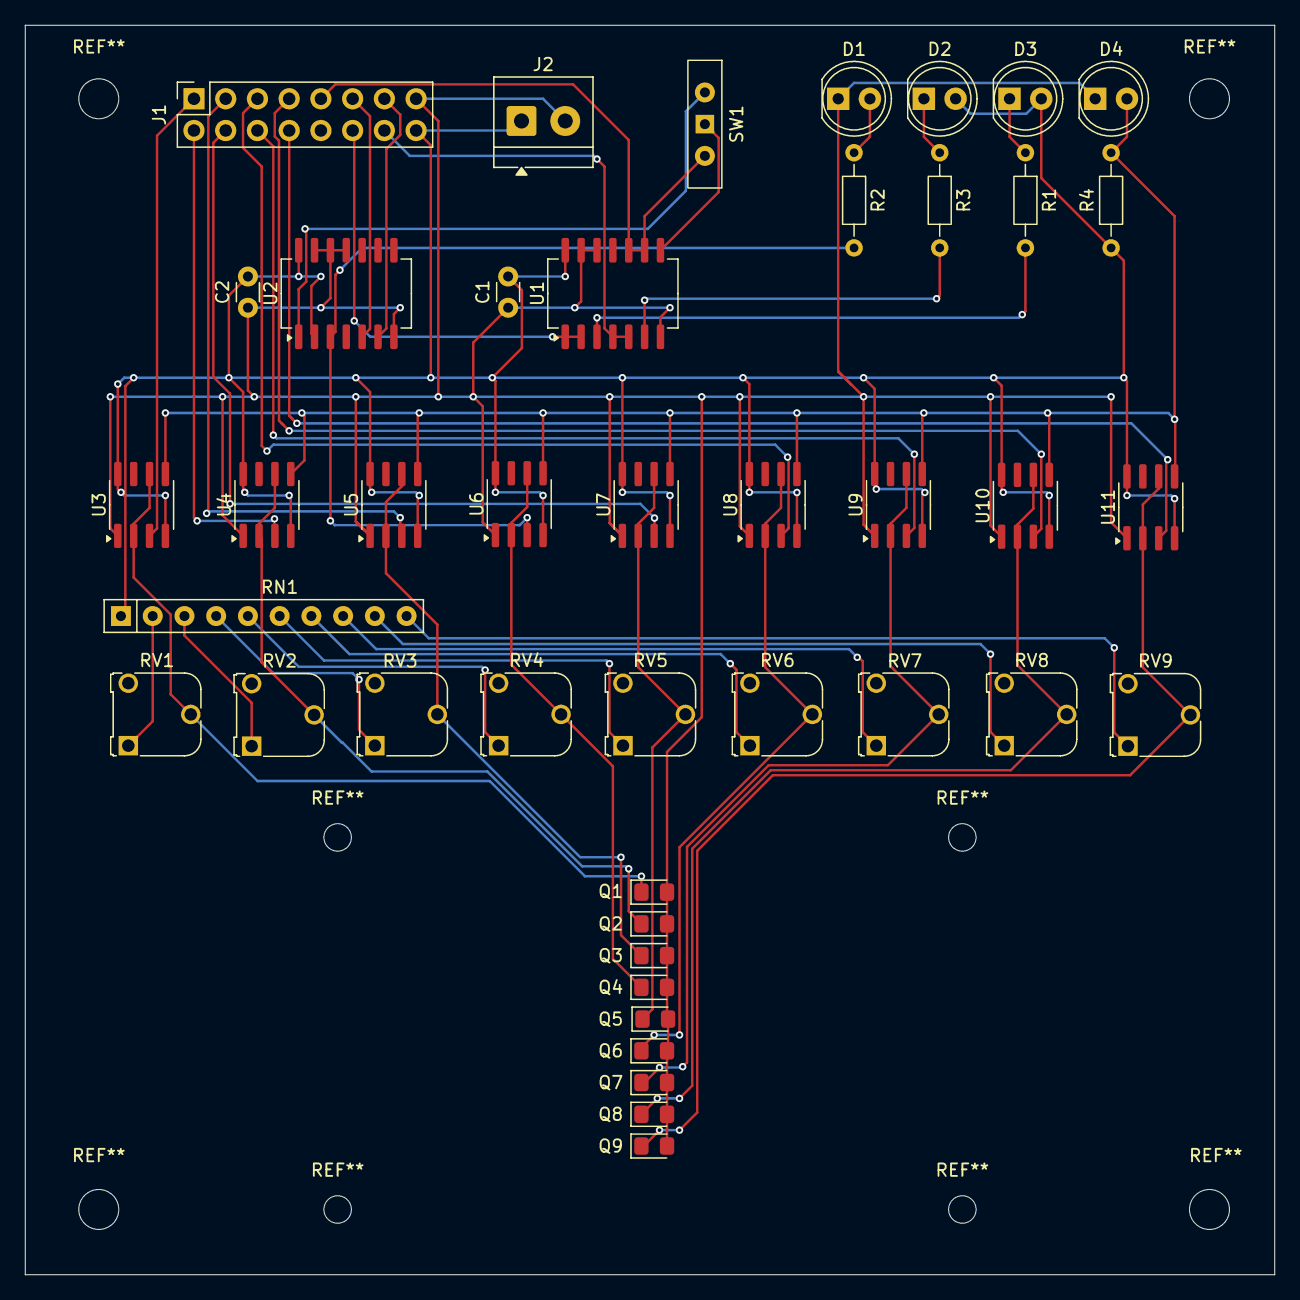
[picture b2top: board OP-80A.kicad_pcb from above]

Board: 2 copper layers, 100.0 x 100.0 mm, 43 parts (0 on the bottom side), 42 nets.
